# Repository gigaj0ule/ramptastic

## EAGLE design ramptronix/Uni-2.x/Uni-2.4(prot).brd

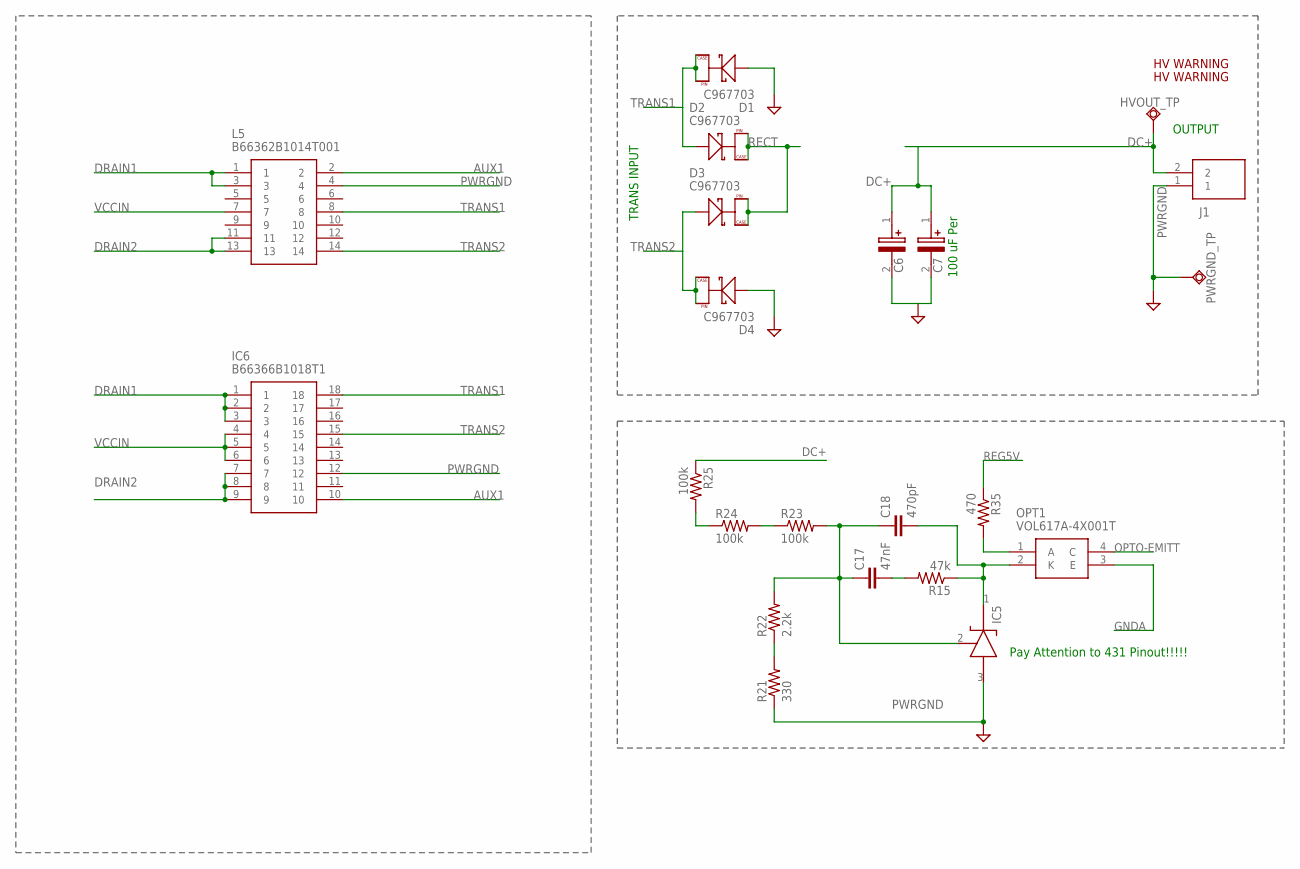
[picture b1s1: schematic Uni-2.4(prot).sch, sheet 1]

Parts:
C6, C7: 400BXW100MEFR18X25; CAPPRD750W80D1825H2700
C17: 47nF; C0603K
C18: 470pF; C0603K
D1, D2, D3, D4: C967703; TO-252
HVOUT_TP: TPSQPAD1-13; P1-13
IC5: cl431; SOT95P280X145-3N
IC6: B66366B1018T1; DIPS3556W80P508L4960H3840Q18N
J1: TB005-762-02BE; TB00576202BE
L5: B66362B1014T001
OPT1: VOL617A-4X001T; SOP254P1015X230-4N
PWRGND_TP: TPSQPAD1-13; P1-13
R15: 47k; R0603
R21: 330; R0805
R22: 2.2k; R0805
R23, R24, R25: 100k; R1206
R35: 470; R0603
U$3, U$4: HV; PSFBC_ELECTRIC_SHOCK

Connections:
AUX1: IC6.10, L5.2; also elsewhere on the board
DC+: C6.1 (+), C7.1 (+), HVOUT_TP.TP, J1.2, R25.1; also elsewhere on the board
DRAIN1: IC6.1, IC6.2, IC6.3, L5.1, L5.3; also elsewhere on the board
DRAIN2: IC6.7, IC6.8, IC6.9, L5.11, L5.13; also elsewhere on the board
GNDA: OPT1.3 (E); also elsewhere on the board
unnamed: R24.1, R25.2
unnamed: C17.1, C18.1, IC5.2 (REF), R22.2, R23.2
unnamed: R23.1, R24.2
unnamed: R21.2, R22.1
unnamed: C18.2, IC5.1 (CATHODE), OPT1.2 (K), R15.1
unnamed: OPT1.1 (A), R35.2
unnamed: C17.2, R15.2
OPTO-EMITT: OPT1.4 (C); also elsewhere on the board
PWRGND: C6.2 (-), C7.2 (-), D1.2 (A), D4.2 (A), IC5.3 (ANODE), IC6.12, J1.1, L5.4, PWRGND_TP.TP, R21.1; also elsewhere on the board
RECT: D2.1 (K_1), D2.3 (K_2), D3.1 (K_1), D3.3 (K_2)
REG5V: R35.1; also elsewhere on the board
TRANS1: D1.1 (K_1), D1.3 (K_2), D2.2 (A), IC6.18, L5.8
TRANS2: D3.2 (A), D4.1 (K_1), D4.3 (K_2), IC6.15, L5.14
VCCIN: IC6.4, IC6.5, IC6.6, L5.7; also elsewhere on the board

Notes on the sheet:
TRANS INPUT
OUTPUT
100 uF Per
Pay Attention to 431 Pinout!!!!!

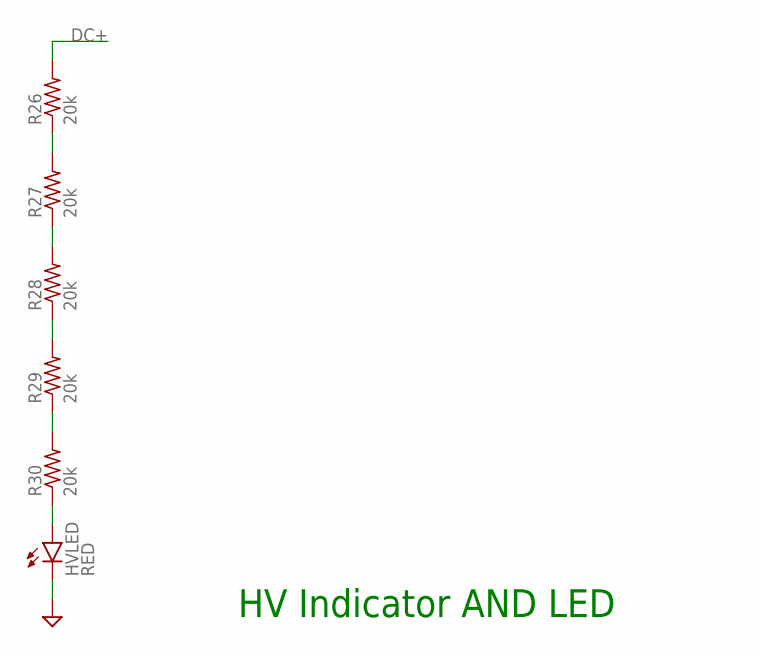
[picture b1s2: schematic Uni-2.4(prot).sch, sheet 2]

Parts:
HVLED: RED; CHIPLED_0805
R26, R27, R28, R29, R30: 20k; R1206

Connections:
DC+: R26.2; also elsewhere on the board
unnamed: HVLED.A, R30.1
unnamed: R29.1, R30.2
unnamed: R28.1, R29.2
unnamed: R27.1, R28.2
unnamed: R26.1, R27.2
PWRGND: HVLED.C; also elsewhere on the board

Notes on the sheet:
HV Indicator AND LED

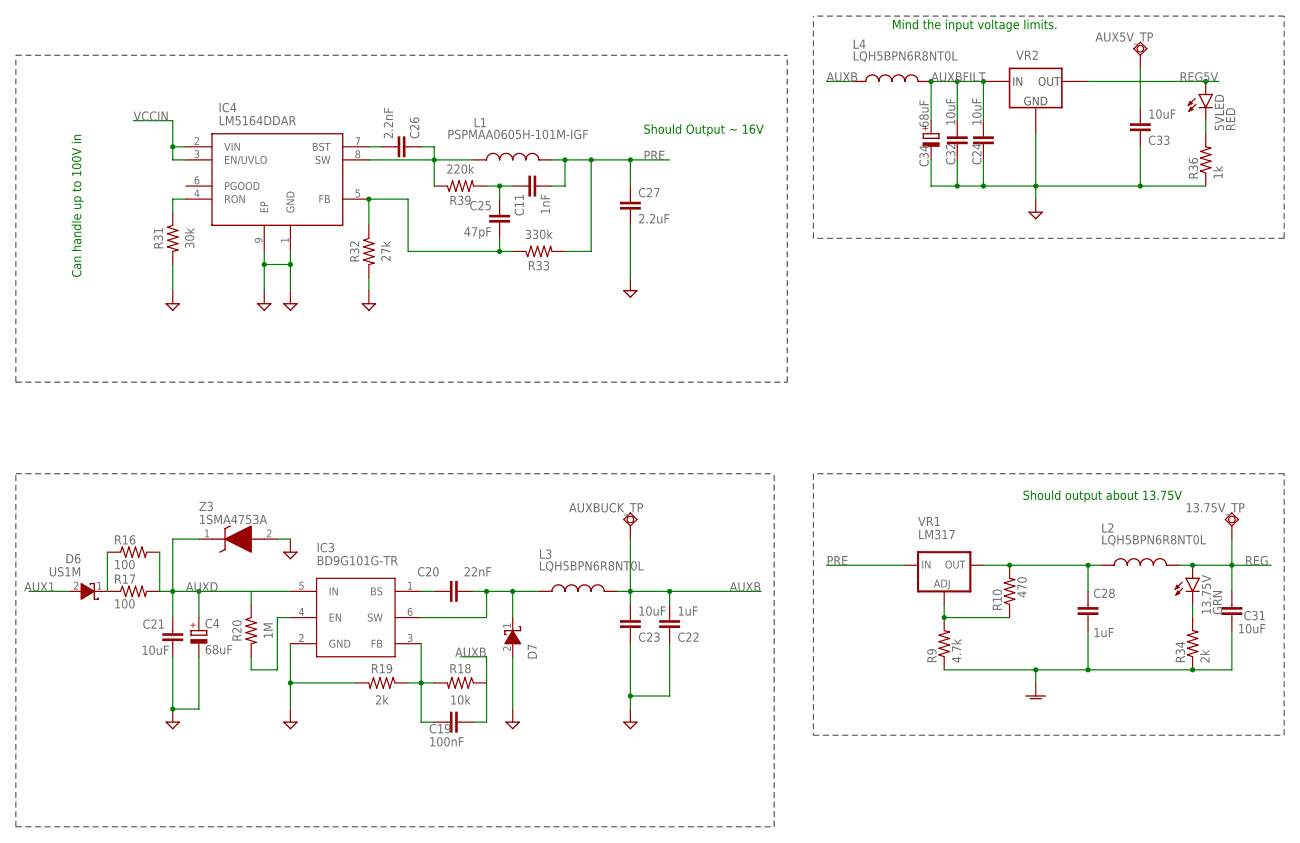
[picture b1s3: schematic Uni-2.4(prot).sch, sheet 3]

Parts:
5VLED: RED; CHIPLED_0805; LCSC_PART C72043
13.75V: GRN; CHIPLED_0805; LCSC_PART C72043
13.75V_TP: TPSQTP18R; TP18R
AUX5V_TP: TPSQPAD1-17; P1-17
AUXBUCK_TP: TPSQTP13R; TP13R
C4, C34: 68uF; UD-8X10_NICHICON; LCSC_PART C249948
C11: 1nF; C0402; LCSC_PART C440198
C19: 100nF; C0402K; LCSC_PART C1546
C20: 22nF; C0603K; LCSC_PART C14663
C21: 10uF; C0805K
C22: 1uF; C0402; LCSC_PART C440198
C23, C24, C31, C32: 10uF; C0603K; LCSC_PART C440198
C25: 47pF; C0402; LCSC_PART C440198
C26: 2.2nF; C0402; LCSC_PART C440198
C27: 2.2uF; C0603K; LCSC_PART C440198
C28: 1uF; C0603K; LCSC_PART C440198
C33: 10uF; C0603K
D6: US1M; DIOM5127X229N
D7: SCHOTTKY; DIOM5127X229N; LCSC_PART C22452
IC3: BD9G101G-TR; SOT95P280X145-6N; LCSC_PART C97643
IC4: LM5164DDAR; SOIC127P600X170-9N
L1: PSPMAA0605H-101M-IGF; LCSC_PART C2983096
L2, L3, L4: LQH5BPN6R8NT0L; LQH5BPB100MT0L
R9: 4.7k; R0603; LCSC_PART C22975
R10: 470; R0603; LCSC_PART C22975
R16, R17: 100; R1206
R18: 10k; R0402; LCSC_PART C25779
R19: 2k; R0402; LCSC_PART C25779
R20: 1M; R0402; LCSC_PART C25741
R31: 30k; R0402; LCSC_PART C25741
R32: 27k; R0603; LCSC_PART C25741
R33: 330k; R0402; LCSC_PART C25741
R34: 2k; R0603; LCSC_PART C22975
R36: 1k; R0603; LCSC_PART C22975
R39: 220k; R0603; LCSC_PART C25741
VR1: LM317; DPACK
VR2: AP2120N-5.0TRG1; SOT95P280X145-3N
Z3: 1SMA4753A; DIOM5226X220N; LCSC_PART C362284

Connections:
AUX1: D6.2 (A); also elsewhere on the board
AUXB: AUXBUCK_TP.TP, C19.1, C22.2, C23.2, L3.2, L4.1, R18.1
AUXBFILT: C24.2, C32.2, C34.+, L4.2, VR2.3 (VIN)
AUXD: C4.+, C21.1, IC3.5 (IN), R16.2, R17.2, R20.1, Z3.1 (K)
BS2: C20.1, IC3.1 (BS)
EN2: IC3.4 (EN), R20.2
FB2: C19.2, IC3.3 (FB), R18.2, R19.1
GND: C27.2, IC4.1 (GND), IC4.9 (EP), R31.2, R32.2
GNDA: C28.2, C31.1, R9.1, R34.1; also elsewhere on the board
unnamed: R9.2, R10.1, VR1.1 (ADJ)
unnamed: IC4.4 (RON), R31.1
unnamed: 13.75V.C, R34.2
unnamed: C26.2, IC4.7 (BST)
unnamed: 5VLED.C, R36.2
unnamed: D6.1 (K), R16.1, R17.1
unnamed: C26.1, IC4.8 (SW), L1.1, R39.1
unnamed: C25.2, IC4.5 (FB), R32.1, R33.1
unnamed: C28.1, L2.1, R10.2, VR1.4 (OUT)
unnamed: C11.1, C25.1, R39.2
PRE: C11.2, C27.1, L1.2, R33.2, VR1.3 (IN)
PWRGND: C4.-, C21.2, C22.1, C23.1, C24.1, C32.1, C33.1, C34.-, D7.2 (A), IC3.2 (GND), R19.2, R36.1, VR2.1 (GND), Z3.2 (A); also elsewhere on the board
REG: 13.75V.A, 13.75V_TP.TP, C31.2, L2.2; also elsewhere on the board
REG5V: 5VLED.A, AUX5V_TP.TP, C33.2, VR2.2 (VOUT); also elsewhere on the board
SWITCH2: C20.2, D7.1 (K), IC3.6 (SW), L3.1
VCCIN: IC4.2 (VIN), IC4.3 (EN/UVLO); also elsewhere on the board

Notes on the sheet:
Should output about 13.75V
Mind the input voltage limits.
Can handle up to 100V in
Should Output ~ 16V

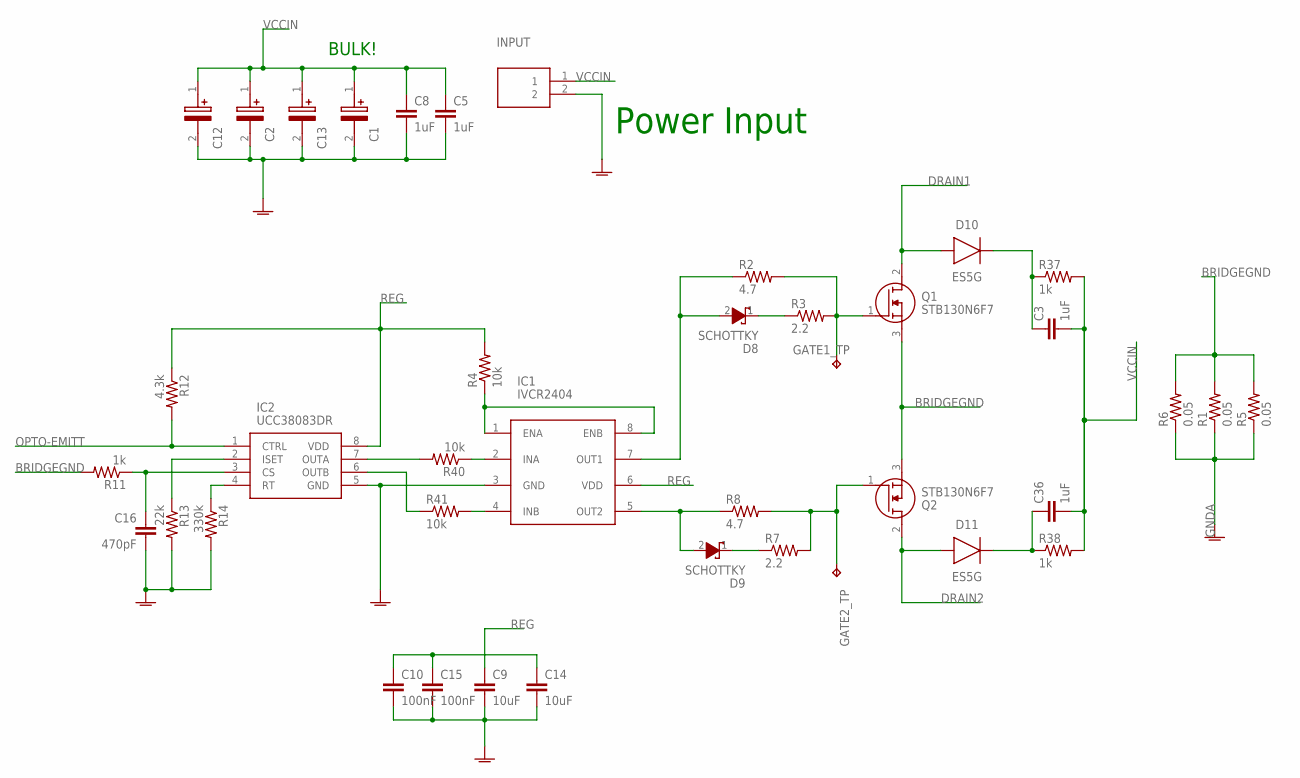
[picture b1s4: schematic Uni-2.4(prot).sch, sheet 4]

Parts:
C1, C2, C12, C13: OVK151M1VTR-10131; 16SVF1000M
C3, C36: 1uF; C1206K
C5, C8: 1uF; C0805K; LCSC_PART C440198
C9, C14: 10uF; C0603K; LCSC_PART C440198
C10, C15: 100nF; C0603K; LCSC_PART C440198
C16: 470pF; C0603K; LCSC_PART C1620
D8, D9: SCHOTTKY; DIOM5127X229N
D10: ES5G; DIOM5336X265N; LCSC_PART C128705
D11: ES5G; DIOM5336X265N
GATE1_TP, GATE2_TP: TPTP13R; TP13R
IC1: IVCR2404; SOIC127P600X175-8N; LCSC_PART C2924635
IC2: UCC38083DR; SOIC127P600X175-8N
INPUT: TB005-762-02BE; TB00576202BE
Q1, Q2: STB130N6F7; D2PAK
R1, R5, R6: 0.05; R2512
R2, R8: 4.7; R0805
R3, R7: 2.2; R0805
R4: 10k; R0402
R11: 1k; R0603; LCSC_PART C21190
R12: 4.3k; R0603; LCSC_PART C22975
R13: 22k; R0603; LCSC_PART C31850
R14: 330k; R0603; LCSC_PART C25811
R37, R38: 1k; R2512
R40, R41: 10k; R0402; LCSC_PART C21190

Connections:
BRIDGEGND: Q1.3 (S), Q2.3 (S), R1.2, R5.2, R6.2, R11.2
CS-IN: C16.1, IC2.3 (CS), R11.1
DRAIN1: D10.2 (A), Q1.2 (D); also elsewhere on the board
DRAIN2: D11.2 (A), Q2.2 (D); also elsewhere on the board
GNDA: C1.2 (-), C2.2 (-), C5.2, C8.2, C9.2, C10.2, C12.2 (-), C13.2 (-), C14.2, C15.2, C16.2, IC1.3 (GND), IC2.5 (GND), INPUT.2, R1.1, R5.1, R6.1, R13.2, R14.2; also elsewhere on the board
unnamed: IC1.2 (INA), R40.1
unnamed: D8.1 (K), R3.1
unnamed: IC1.4 (INB), R41.2
unnamed: IC1.1 (ENA), IC1.8 (ENB), R4.1
unnamed: D8.2 (A), IC1.7 (OUT1), R2.1
unnamed: D9.2 (A), IC1.5 (OUT2), R8.1
unnamed: D9.1 (K), R7.1
unnamed: IC2.2 (ISET), R13.1
unnamed: C3.1, D10.1 (C), R37.1
unnamed: C36.1, D11.1 (C), R38.1
unnamed: IC2.6 (OUTB), R41.1
unnamed: IC2.7 (OUTA), R40.2
OPTO-EMITT: IC2.1 (CTRL), R12.2; also elsewhere on the board
Q1G: GATE1_TP.TP, Q1.1 (G), R2.2, R3.2
Q2G: GATE2_TP.TP, Q2.1 (G), R7.2, R8.2
REG: C9.1, C10.1, C14.1, C15.1, IC1.6 (VDD), IC2.8 (VDD), R4.2, R12.1; also elsewhere on the board
RT: IC2.4 (RT), R14.1
VCCIN: C1.1 (+), C2.1 (+), C3.2, C5.1, C8.1, C12.1 (+), C13.1 (+), C36.2, INPUT.1, R37.2, R38.2; also elsewhere on the board

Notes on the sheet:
BULK!
Power Input

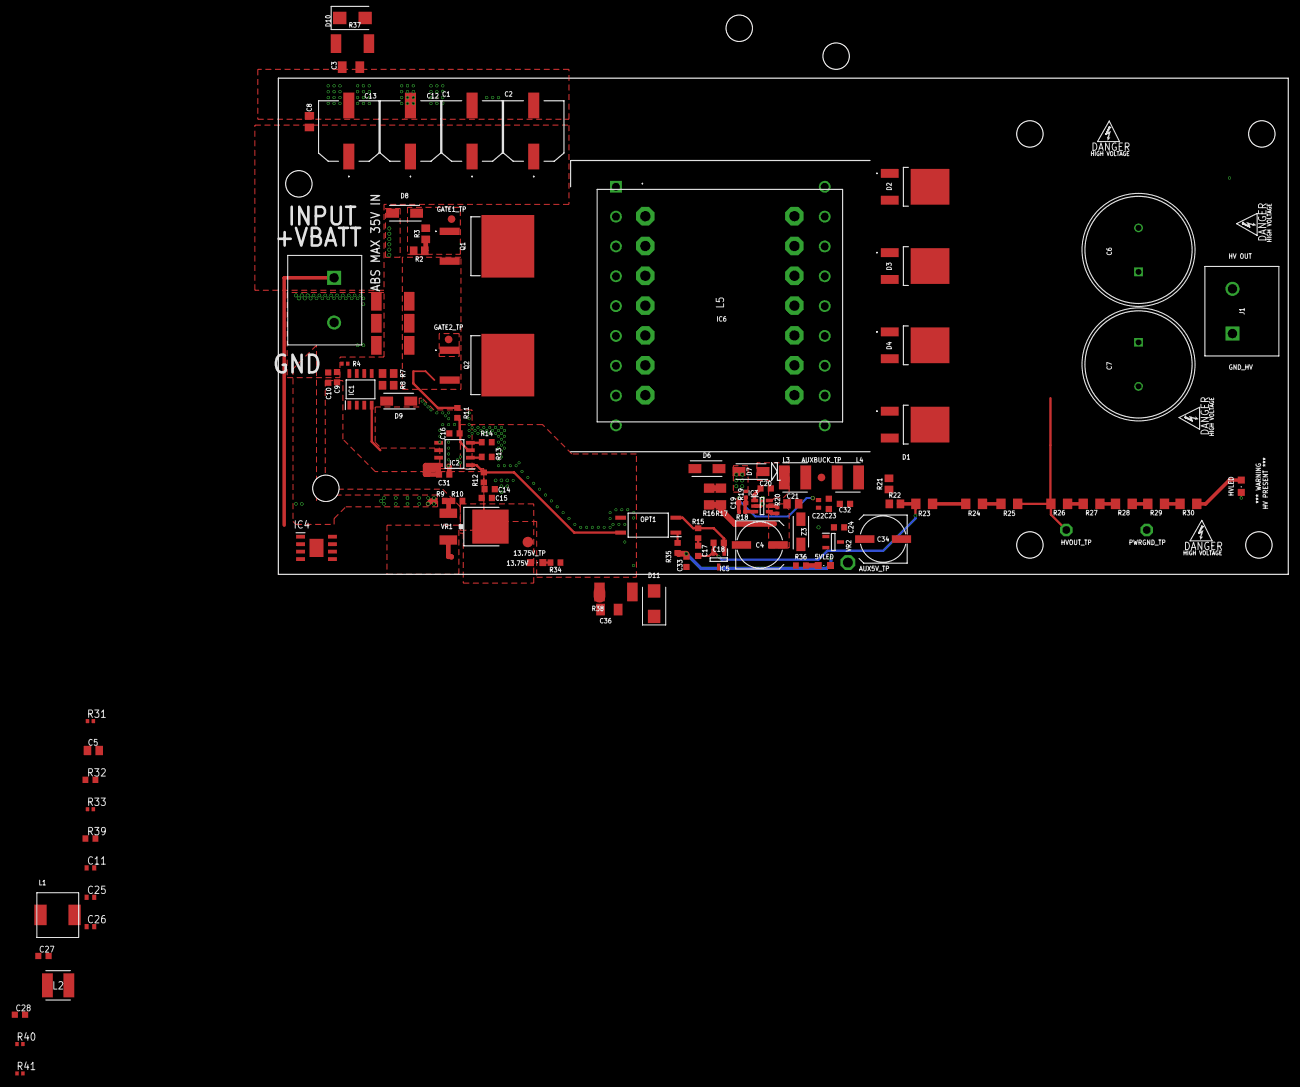
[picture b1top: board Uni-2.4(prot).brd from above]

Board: 4 copper layers, 172.0 x 84.5 mm, 117 parts (0 on the bottom side), 61 nets.

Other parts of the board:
U$1, U$2: HV; PSFBC_ELECTRIC_SHOCK

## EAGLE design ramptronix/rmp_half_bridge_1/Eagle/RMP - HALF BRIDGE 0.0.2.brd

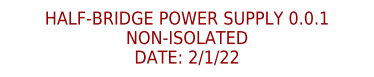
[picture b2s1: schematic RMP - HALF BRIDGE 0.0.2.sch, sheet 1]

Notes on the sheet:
HALF-BRIDGE POWER SUPPLY 0.0.1 NON-ISOLATED DATE: 2/1/22

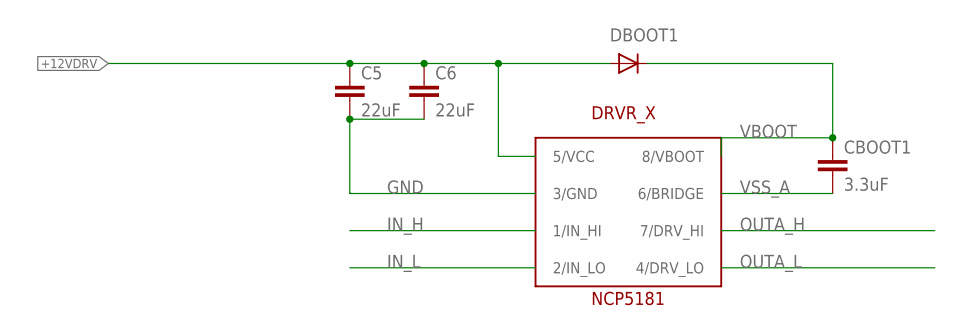
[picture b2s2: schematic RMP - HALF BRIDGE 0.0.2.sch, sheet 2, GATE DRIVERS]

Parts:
C5, C6: 22uF; C1206; LCSC_PART C77091
CBOOT1: 3.3uF; C1812; LCSC_PART C342636
DBOOT1: DIODESMA; SMADIODE; LCSC_PART C110531
DRVR_X: NCP5181; 8-SOIC; LCSC_PART DNP

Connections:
+12VDRV: C5.1, C6.1, DBOOT1.A, DRVR_X.5 (5/VCC); also elsewhere on the board
GND: C5.2, C6.2, DRVR_X.3 (3/GND); also elsewhere on the board
IN_H: DRVR_X.1 (1/IN_HI); also elsewhere on the board
IN_L: DRVR_X.2 (2/IN_LO); also elsewhere on the board
OUTA_H: DRVR_X.7 (7/DRV_HI); also elsewhere on the board
OUTA_L: DRVR_X.4 (4/DRV_LO); also elsewhere on the board
VBOOT: CBOOT1.1, DBOOT1.C, DRVR_X.8 (8/VBOOT)
VSS_A: CBOOT1.2, DRVR_X.6 (6/BRIDGE); also elsewhere on the board

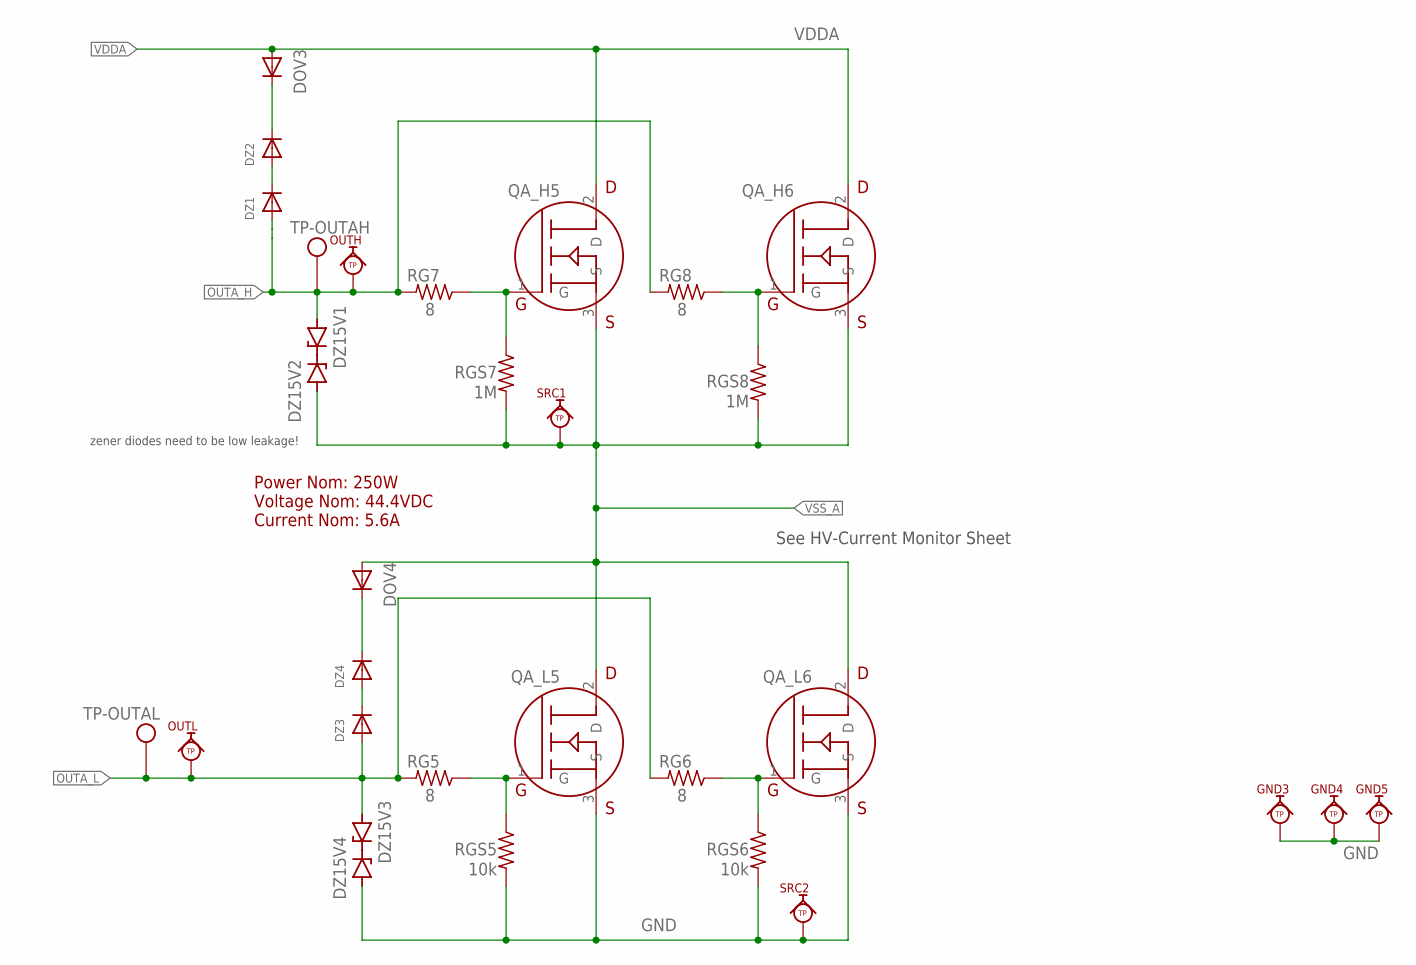
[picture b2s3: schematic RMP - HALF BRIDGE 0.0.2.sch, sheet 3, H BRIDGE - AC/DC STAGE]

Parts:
DOV3, DOV4: DIODESMA; SMADIODE; LCSC_PART C110531
DZ1, DZ2, DZ3, DZ4: DIODESMA; SMADIODE; LCSC_PART C362303
DZ15V1, DZ15V2, DZ15V3, DZ15V4: NZH15B,115; SODFL3718X115; LCSC_PART C173428
GND3, GND4, GND5: KEYSTONE_5190_SMT
OUTH: KEYSTONE_5190_SMT
OUTL: KEYSTONE_5190_SMT
QA_H5, QA_H6: IPB60R060P7ATMA1; D2PACK; LCSC_PART C604524
QA_L5, QA_L6: IPB60R060P7ATMA1; D2PACK; LCSC_PART C604524
RG5, RG6, RG7, RG8: 8; R1206; LCSC_PART C118070
RGS5, RGS6: 10k; R1206; LCSC_PART C140407
RGS7, RGS8: 1M; R1206; LCSC_PART C105578
SRC1, SRC2: KEYSTONE_5190_SMT
TP-OUTAH: THM_TESTPOINT_5000_SERIES; THM-TESTPOINT; LCSC_PART DNP
TP-OUTAL: THM_TESTPOINT_5000_SERIES; THM-TESTPOINT; LCSC_PART DNP

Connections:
GND: DZ15V4.2 (A), GND3.P$1, GND4.P$1, GND5.P$1, QA_L5.3 (S), QA_L6.3 (S), RGS5.2, RGS6.2, SRC2.P$1; also elsewhere on the board
unnamed: DZ1.C, DZ2.A
unnamed: DOV4.C, DZ4.C
unnamed: DZ3.C, DZ4.A
unnamed: DZ15V3.1 (C), DZ15V4.1 (C)
unnamed: DZ15V1.1 (C), DZ15V2.1 (C)
unnamed: QA_L6.1 (G), RG6.1, RGS6.1
unnamed: QA_H6.1 (G), RG8.1, RGS8.1
unnamed: QA_H5.1 (G), RG7.1, RGS7.1
unnamed: QA_L5.1 (G), RG5.1, RGS5.1
unnamed: DOV3.C, DZ2.C
OUTA_H: DZ1.A, DZ15V1.2 (A), OUTH.P$1, RG7.2, RG8.2, TP-OUTAH.P1; also elsewhere on the board
OUTA_L: DZ3.A, DZ15V3.2 (A), OUTL.P$1, RG5.2, RG6.2, TP-OUTAL.P1; also elsewhere on the board
VDDA: DOV3.A, QA_H5.2 (D), QA_H6.2 (D); also elsewhere on the board
VSS_A: DOV4.A, DZ15V2.2 (A), QA_H5.3 (S), QA_H6.3 (S), QA_L5.2 (D), QA_L6.2 (D), RGS7.2, RGS8.2, SRC1.P$1; also elsewhere on the board

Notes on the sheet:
See HV-Current Monitor Sheet
Power Nom: 250W Voltage Nom: 44.4VDC Current Nom: 5.6A
zener diodes need to be low leakage!

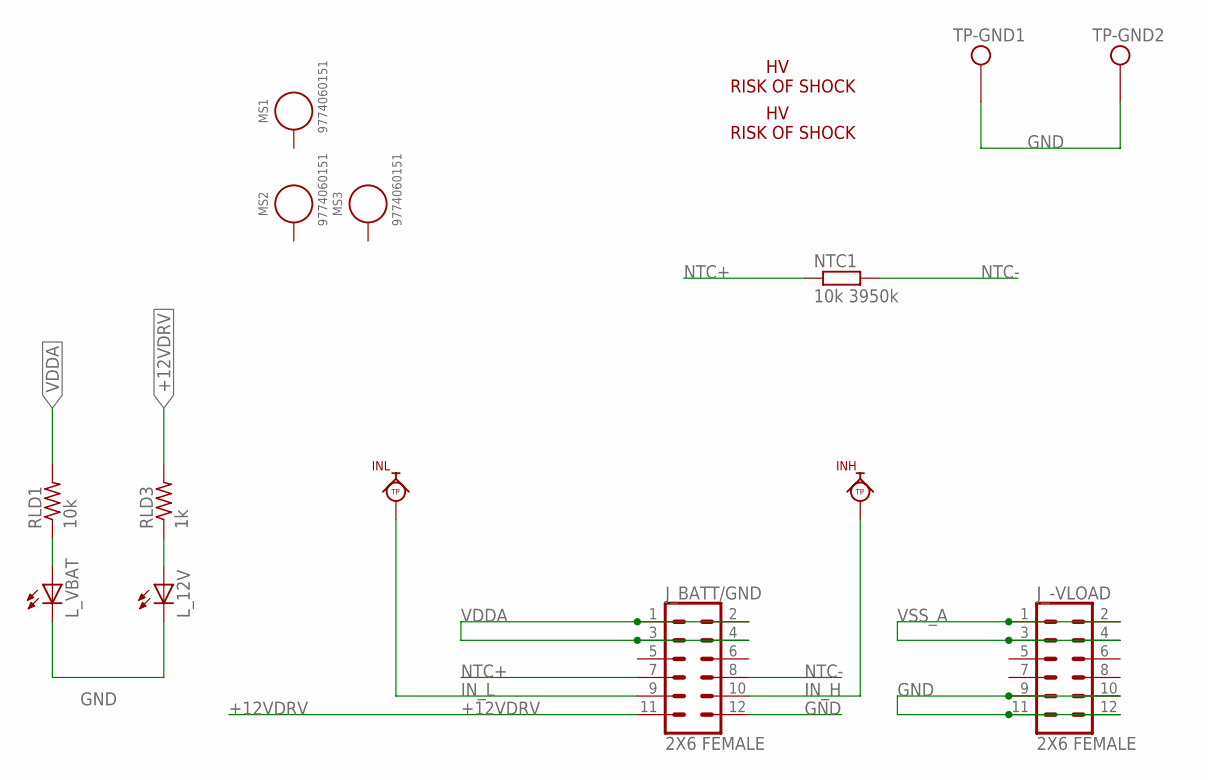
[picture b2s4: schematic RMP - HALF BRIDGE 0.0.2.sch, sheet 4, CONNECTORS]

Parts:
INH: KEYSTONE_5190_SMT
INL: KEYSTONE_5190_SMT
J_-VLOAD: 2X6 FEMALE; 2X6; LCSC_PART DNP
J_BATT/GND: 2X6 FEMALE; 2X6; LCSC_PART DNP
L_12V: LEDCHIPLED_1206; CHIPLED_1206; LCSC_PART C434439
L_VBAT: LEDCHIPLED_1206; CHIPLED_1206; LCSC_PART C434439
MS1, MS2, MS3: 9774060151; WA-SMSI_9774060151; LCSC_PART DNP
NTC1: 10k 3950k; R0805; LCSC_PART C95968
RLD1: 10k; R1206; LCSC_PART C140407
RLD3: 1k; R1206; LCSC_PART C115421
TP-GND1, TP-GND2: THM_TESTPOINT_5000_SERIES; THM-TESTPOINT; LCSC_PART DNP
U$10, U$11: ELECTRIC_SHOCK; LCSC_PART DNP

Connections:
+12VDRV: J_BATT/GND.11, RLD3.2; also elsewhere on the board
GND: J_-VLOAD.9, J_-VLOAD.10, J_-VLOAD.11, J_-VLOAD.12, J_BATT/GND.12, L_12V.C, L_VBAT.C, TP-GND1.P1, TP-GND2.P1; also elsewhere on the board
IN_H: INH.P$1, J_BATT/GND.10; also elsewhere on the board
IN_L: INL.P$1, J_BATT/GND.9; also elsewhere on the board
unnamed: L_VBAT.A, RLD1.1
unnamed: L_12V.A, RLD3.1
NTC+: J_BATT/GND.7, NTC1.1
NTC-: J_BATT/GND.8, NTC1.2
VDDA: J_BATT/GND.1, J_BATT/GND.2, J_BATT/GND.3, J_BATT/GND.4, RLD1.2; also elsewhere on the board
VSS_A: J_-VLOAD.1, J_-VLOAD.2, J_-VLOAD.3, J_-VLOAD.4; also elsewhere on the board

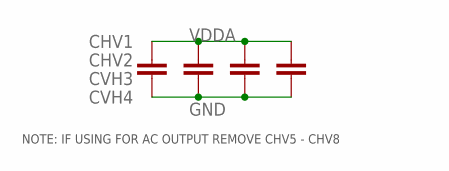
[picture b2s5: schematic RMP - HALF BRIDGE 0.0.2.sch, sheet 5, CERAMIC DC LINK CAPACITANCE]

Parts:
CHV1, CHV2: 3.3uF, 100V; C2220K; LCSC_PART DNP/C342270
CVH3, CVH4: 3.3uF, 100V; C2220K; LCSC_PART DNP/C342270

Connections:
GND: CHV1.2, CHV2.2, CVH3.2, CVH4.2; also elsewhere on the board
VDDA: CHV1.1, CHV2.1, CVH3.1, CVH4.1; also elsewhere on the board

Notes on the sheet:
NOTE: IF USING FOR AC OUTPUT REMOVE CHV5 - CHV8

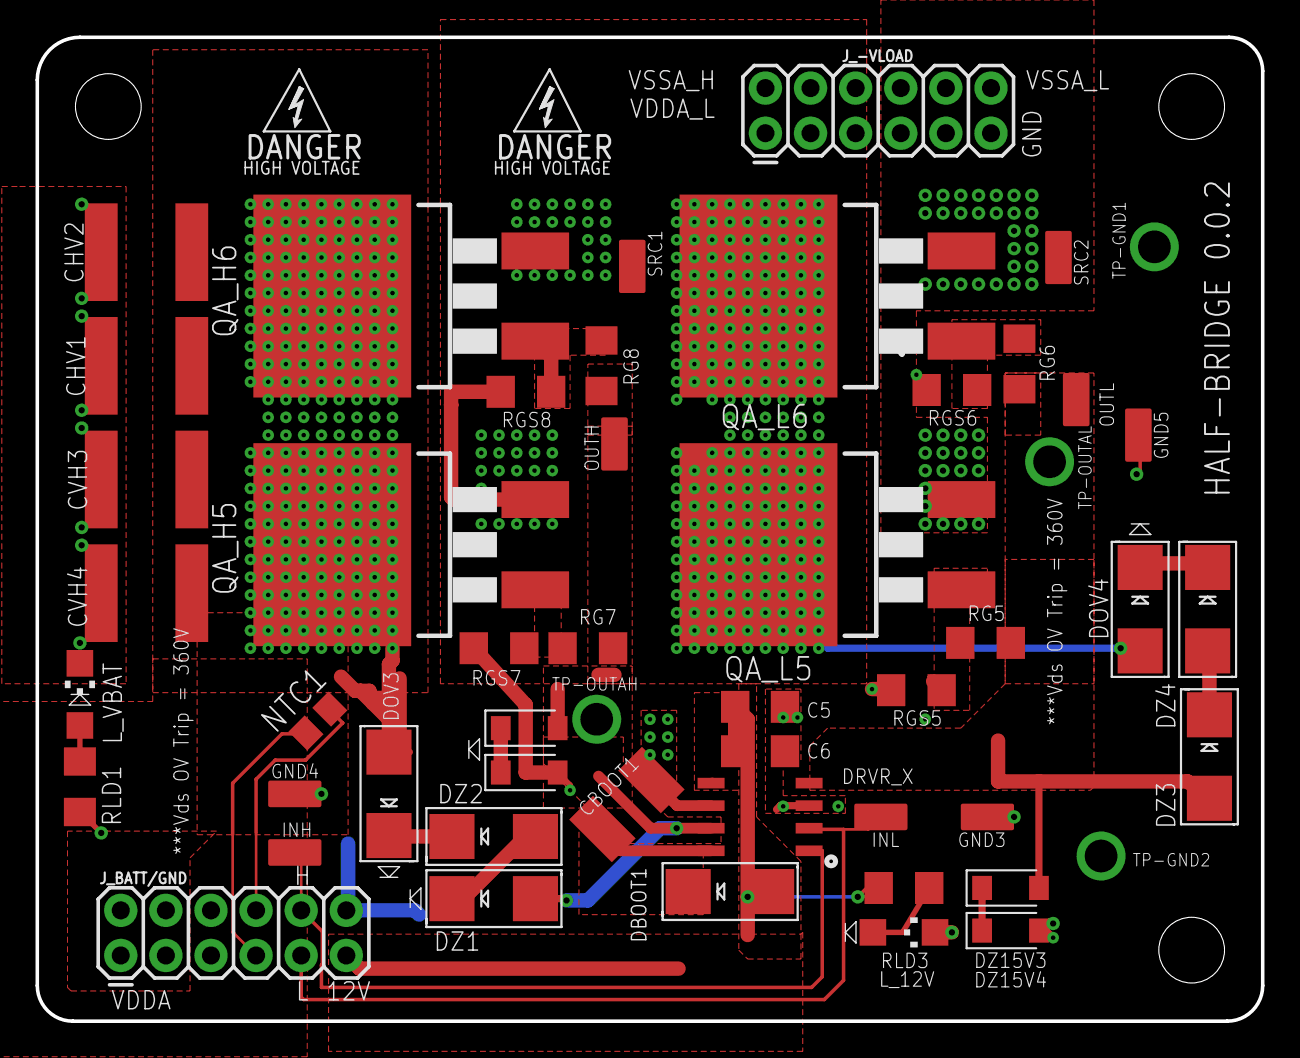
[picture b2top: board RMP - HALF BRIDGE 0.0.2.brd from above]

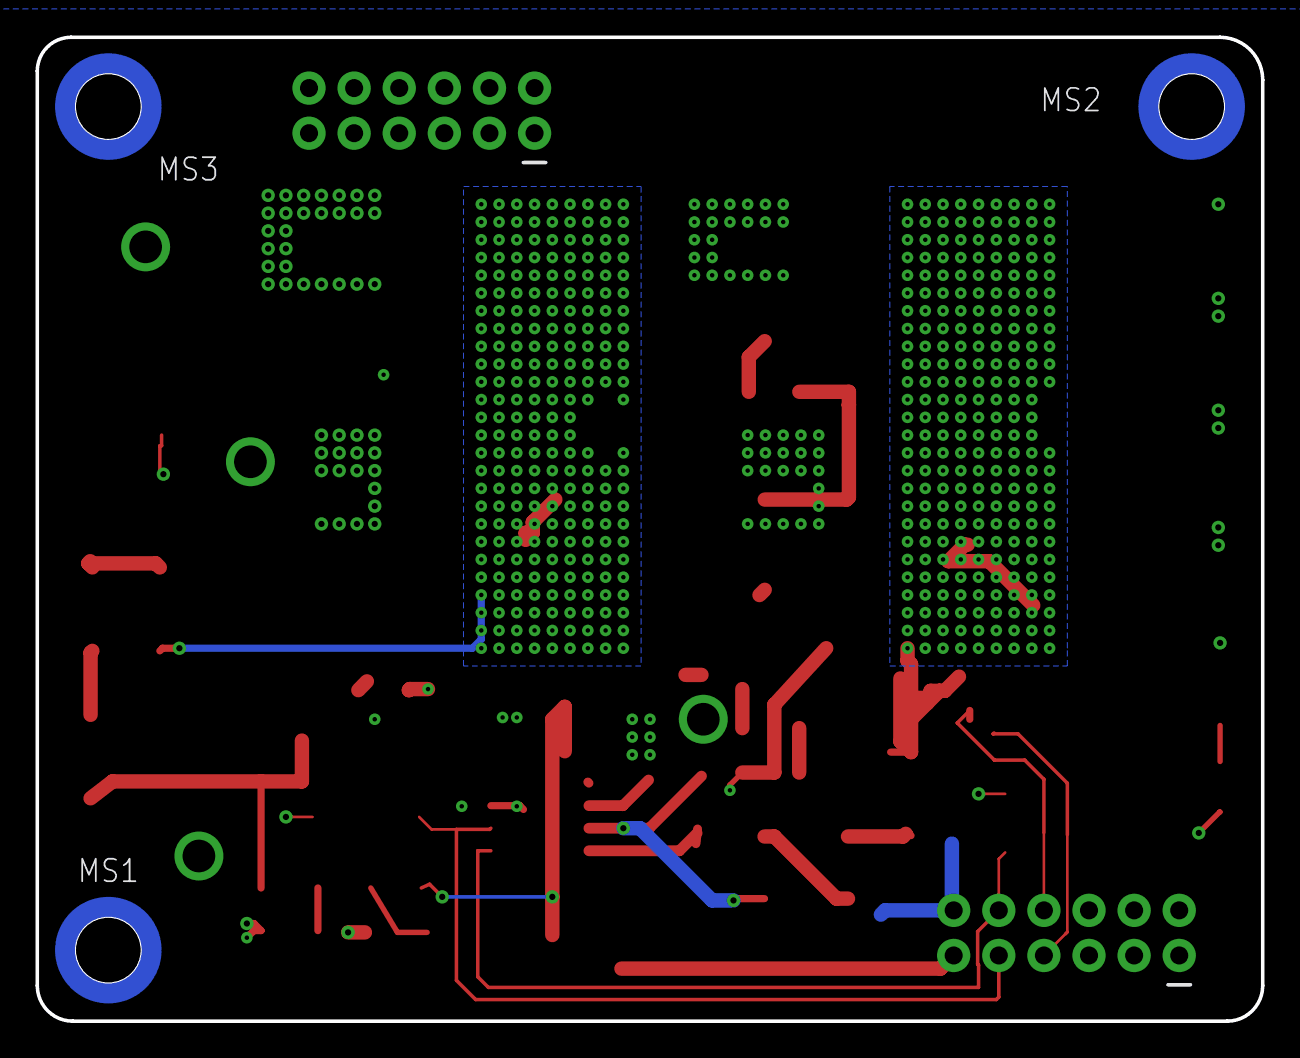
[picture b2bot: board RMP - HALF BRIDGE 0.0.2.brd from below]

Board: 4 copper layers, 69.0 x 55.4 mm, 56 parts (3 on the bottom side), 23 nets.

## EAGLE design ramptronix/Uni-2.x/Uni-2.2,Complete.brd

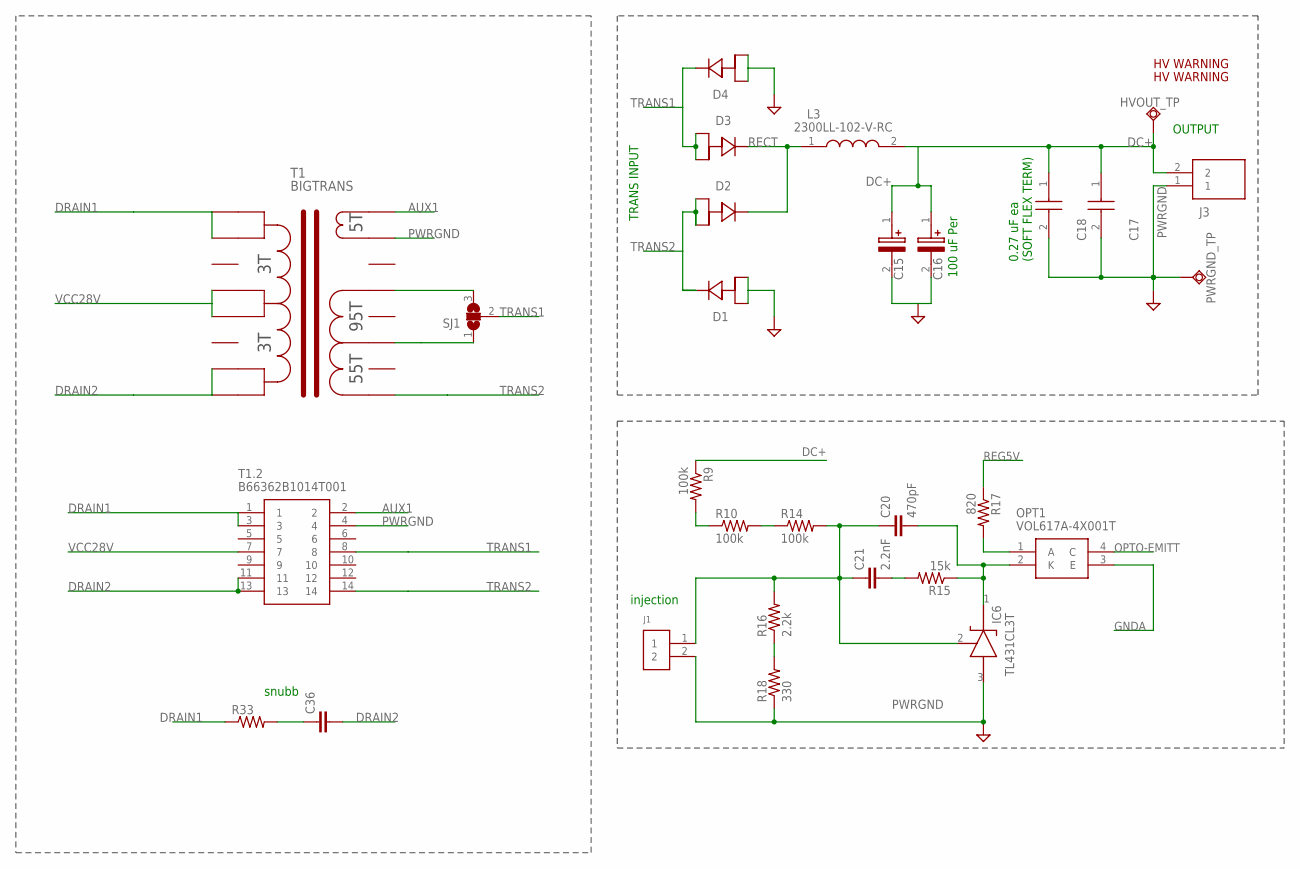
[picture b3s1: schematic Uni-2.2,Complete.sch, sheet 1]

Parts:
C15, C16: 400BXW100MEFR18X25; CAPPRD750W80D1825H2700
C17, C18: C1812C274KCRACAUTO; C1812
C20: 470pF; C0603K
C21: 2.2nF; C0603K
C36: C-EUC1210K; C1210K
D1, D2, D3, D4: FERD20H60CG-TR; STB20N95K5
HVOUT_TP: TPSQPAD1-13; P1-13
IC6: TL431CL3T; SOT95P237X112-3N
J1: 61300211121
J3: TB005-762-02BE; TB00576202BE
L3: 2300LL-102-V-RC; 2300LL102VRC
OPT1: VOL617A-4X001T; SOP254P1015X230-4N
PWRGND_TP: TPSQPAD1-13; P1-13
R9, R10, R14: 100k; R1206
R15: 15k; R0603
R16: 2.2k; R0805
R17: 820; R0603
R18: 330; R0805
R33: R-US_R1206; R1206
SJ1: SJ2WW; SJ_2W
T1: BIGTRANS; BIGTRANS!
T1.2: B66362B1014T001
U$2, U$3: HV; PSFBC_ELECTRIC_SHOCK

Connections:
AUX1: T1.16, T1.2.2; also elsewhere on the board
DC+: C15.1 (+), C16.1 (+), C17.1, C18.1, HVOUT_TP.TP, J3.2, L3.2, R9.1; also elsewhere on the board
DRAIN1: R33.1, T1.7, T1.8, T1.2.1, T1.2.3; also elsewhere on the board
DRAIN2: C36.2, T1.1, T1.2, T1.2.11, T1.2.13; also elsewhere on the board
GNDA: OPT1.3 (E); also elsewhere on the board
unnamed: R9.2, R10.1
unnamed: C20.1, C21.1, IC6.2 (REF), J1.1, R14.2, R16.2
unnamed: SJ1.1, T1.11
unnamed: R10.2, R14.1
unnamed: R16.1, R18.2
unnamed: C20.2, IC6.1 (CATHODE), OPT1.2 (K), R15.1
unnamed: OPT1.1 (A), R17.2
unnamed: C21.2, R15.2
unnamed: SJ1.3, T1.13
unnamed: C36.1, R33.2
OPTO-EMITT: OPT1.4 (C); also elsewhere on the board
PWRGND: C15.2 (-), C16.2 (-), C17.2, C18.2, D1.1 (A1), D1.3 (A2), D4.1 (A1), D4.3 (A2), IC6.3 (ANODE), J1.2, J3.1, PWRGND_TP.TP, R18.1, T1.15, T1.2.4; also elsewhere on the board
RECT: D2.2 (K), D3.2 (K), L3.1
REG5V: R17.1; also elsewhere on the board
TRANS1: D3.1 (A1), D3.3 (A2), D4.2 (K), SJ1.2, T1.2.8
TRANS2: D1.2 (K), D2.1 (A1), D2.3 (A2), T1.9, T1.2.14
VCC28V: T1.4, T1.5, T1.2.7; also elsewhere on the board

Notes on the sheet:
TRANS INPUT
OUTPUT
snubb
injection
100 uF Per
0.27 uF ea (SOFT FLEX TERM)

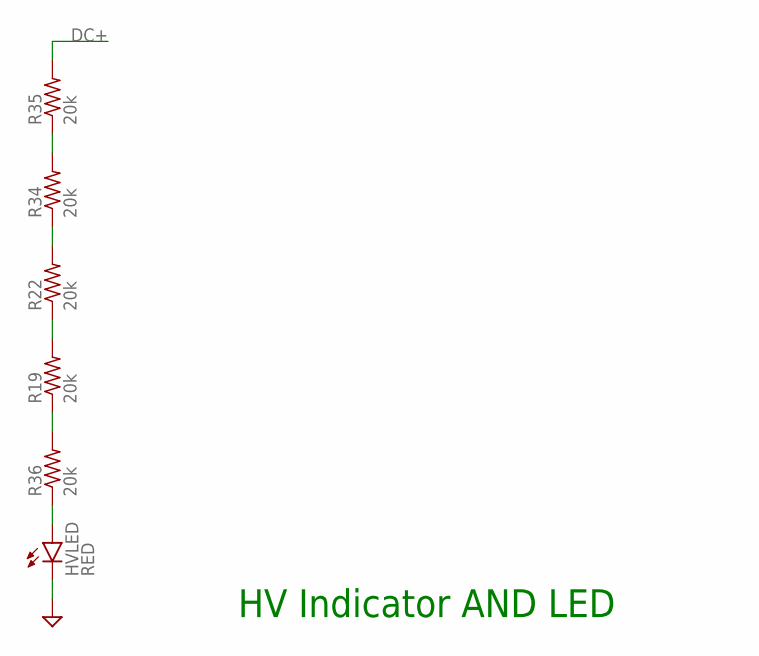
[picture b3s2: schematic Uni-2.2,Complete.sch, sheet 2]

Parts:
HVLED: RED; CHIPLED_0805
R19, R22, R34, R35, R36: 20k; R1206

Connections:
DC+: R35.2; also elsewhere on the board
unnamed: HVLED.A, R36.1
unnamed: R19.1, R36.2
unnamed: R19.2, R22.1
unnamed: R22.2, R34.1
unnamed: R34.2, R35.1
PWRGND: HVLED.C; also elsewhere on the board

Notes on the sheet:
HV Indicator AND LED

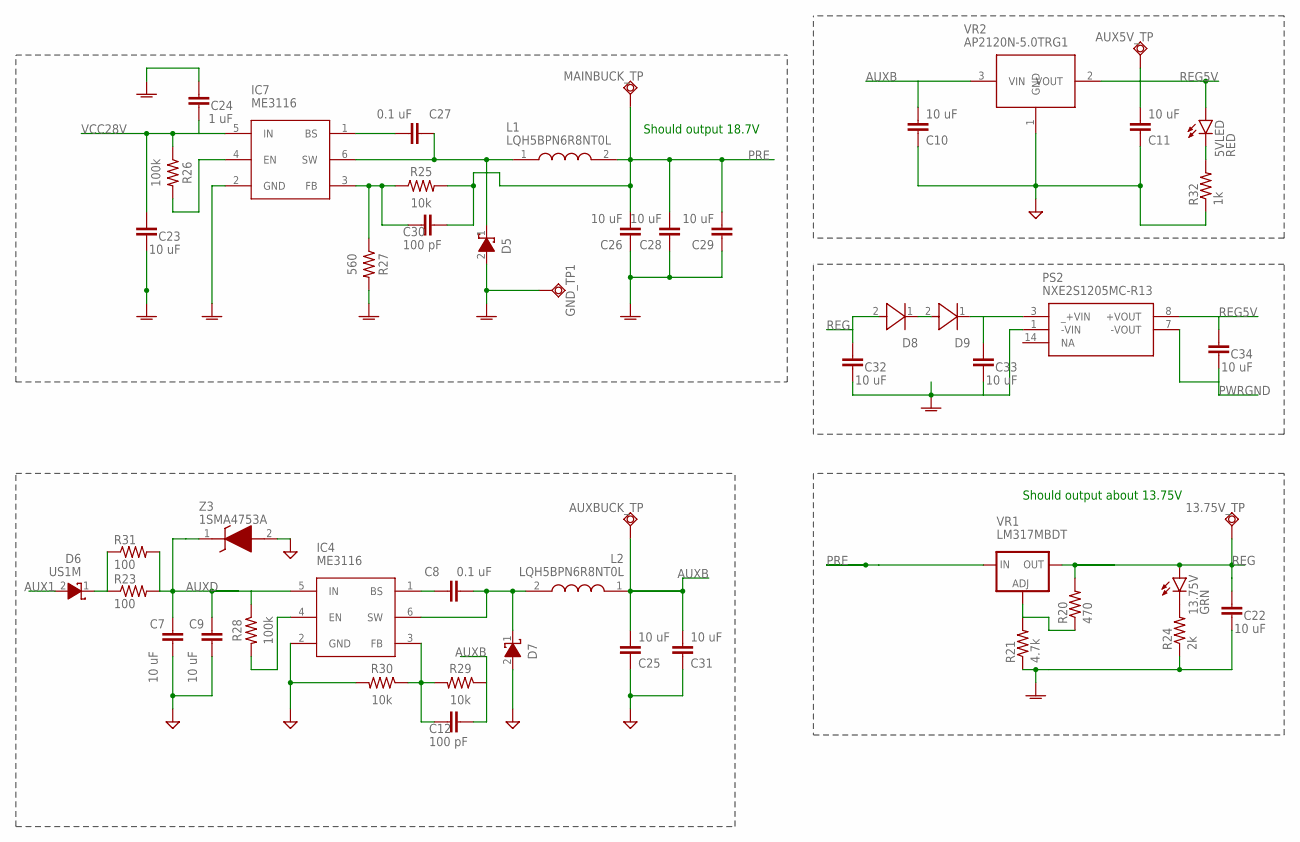
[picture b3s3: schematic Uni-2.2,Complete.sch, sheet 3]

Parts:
5VLED: RED; CHIPLED_0805; LCSC_PART C72043
13.75V: GRN; CHIPLED_0805; LCSC_PART C72043
13.75V_TP: TPSQPAD1-17; P1-17
AUX5V_TP: TPSQPAD1-17; P1-17
AUXBUCK_TP: TPSQPAD1-17; P1-17
C7, C9: 10 uF; C0805K
C8, C27: 0.1 uF; C0603K; LCSC_PART C14663
C10, C25, C33, C34: 10 uF; C0603K; LCSC_PART C440198
C11: 10 uF; C0603K
C12, C30: 100 pF; C0402K; LCSC_PART C1546
C22, C23, C26, C28, C29, C32: 10 uF; C0805K; LCSC_PART C440198
C24: 1 uF; C0603K; LCSC_PART C440198
C31: 10 uF; C0402; LCSC_PART C440198
D5, D7: SCHOTTKY; DIOM5127X229N; LCSC_PART C22452
D6: US1M; DIOM5127X229N
D8, D9: SM4007PL; SOD3716X145N; LCSC_PART C64898
GND_TP1: TPSQPAD1-13; P1-13
IC4, IC7: ME3116; SOT95P280X100-6N; LCSC_PART C97643
L1, L2: LQH5BPN6R8NT0L; LQH5BPB100MT0L
MAINBUCK_TP: TPSQPAD1-17; P1-17
PS2: NXE2S1205MC-R13; NXE2S1205MCR13
R20: 470; R0603; LCSC_PART C22975
R21: 4.7k; R0603; LCSC_PART C22975
R23, R31: 100; R1206
R24: 2k; R0603; LCSC_PART C22975
R25, R29, R30: 10k; R0402; LCSC_PART C25779
R26, R28: 100k; R0402; LCSC_PART C25741
R27: 560; R0402; LCSC_PART C4177
R32: 1k; R0603; LCSC_PART C22975
VR1: LM317MBDT; DPACK
VR2: AP2120N-5.0TRG1; SOT95P240X120-3N
Z3: 1SMA4753A; DIOM5226X220N; LCSC_PART C362284

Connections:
AUX1: D6.2 (A); also elsewhere on the board
AUXB: AUXBUCK_TP.TP, C10.2, C12.1, C25.2, C31.2, L2.1, R29.1, VR2.3 (VIN)
AUXD: C7.1, C9.1, IC4.5 (IN), R23.2, R28.1, R31.2, Z3.1 (K)
BS1: C27.2, IC7.1 (BS)
BS2: C8.1, IC4.1 (BS)
EN1: IC7.4 (EN), R26.2
EN2: IC4.4 (EN), R28.2
FB1: C30.2, IC7.3 (FB), R25.1, R27.1
FB2: C12.2, IC4.3 (FB), R29.2, R30.1
GNDA: C22.1, C23.1, C24.2, C26.1, C28.1, C29.1, C32.1, C33.1, D5.2 (A), GND_TP1.TP, IC7.2 (GND), PS2.1 (-VIN), R21.1, R24.1, R27.2; also elsewhere on the board
unnamed: D8.1 (K), D9.2 (A)
unnamed: R20.1, R21.2, VR1.1 (ADJ)
unnamed: C33.2, D9.1 (K), PS2.3 (_+VIN)
unnamed: 13.75V.C, R24.2
unnamed: 5VLED.C, R32.2
unnamed: D6.1 (K), R23.1, R31.1
PRE: C26.2, C28.2, C29.2, C30.1, L1.2, MAINBUCK_TP.TP, R25.2, VR1.3 (IN)
PWRGND: C7.2, C9.2, C10.1, C11.1, C25.1, C31.1, C34.1, D7.2 (A), IC4.2 (GND), PS2.7 (-VOUT), R30.2, R32.1, VR2.1 (GND), Z3.2 (A); also elsewhere on the board
REG: 13.75V.A, 13.75V_TP.TP, C22.2, C32.2, D8.2 (A), R20.2, VR1.4 (OUT); also elsewhere on the board
REG5V: 5VLED.A, AUX5V_TP.TP, C11.2, C34.2, PS2.8 (+VOUT), VR2.2 (VOUT); also elsewhere on the board
SWITCH1: C27.1, D5.1 (K), IC7.6 (SW), L1.1
SWITCH2: C8.2, D7.1 (K), IC4.6 (SW), L2.2
VCC28V: C23.2, C24.1, IC7.5 (IN), R26.1; also elsewhere on the board

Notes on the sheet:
Should output 18.7V
Should output about 13.75V

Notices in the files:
parts and their libraries:
SparkFun-Connectors: Licensing: Creative Commons ShareAlike 4.0 International - https://creativecommons.org/licenses/by-sa/4.0
Eagle_WA-SMSI: Copyright: Würth Elektronik
